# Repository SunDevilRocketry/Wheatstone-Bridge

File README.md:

# L0003 Wheatstone Bridge
Rev 1.0

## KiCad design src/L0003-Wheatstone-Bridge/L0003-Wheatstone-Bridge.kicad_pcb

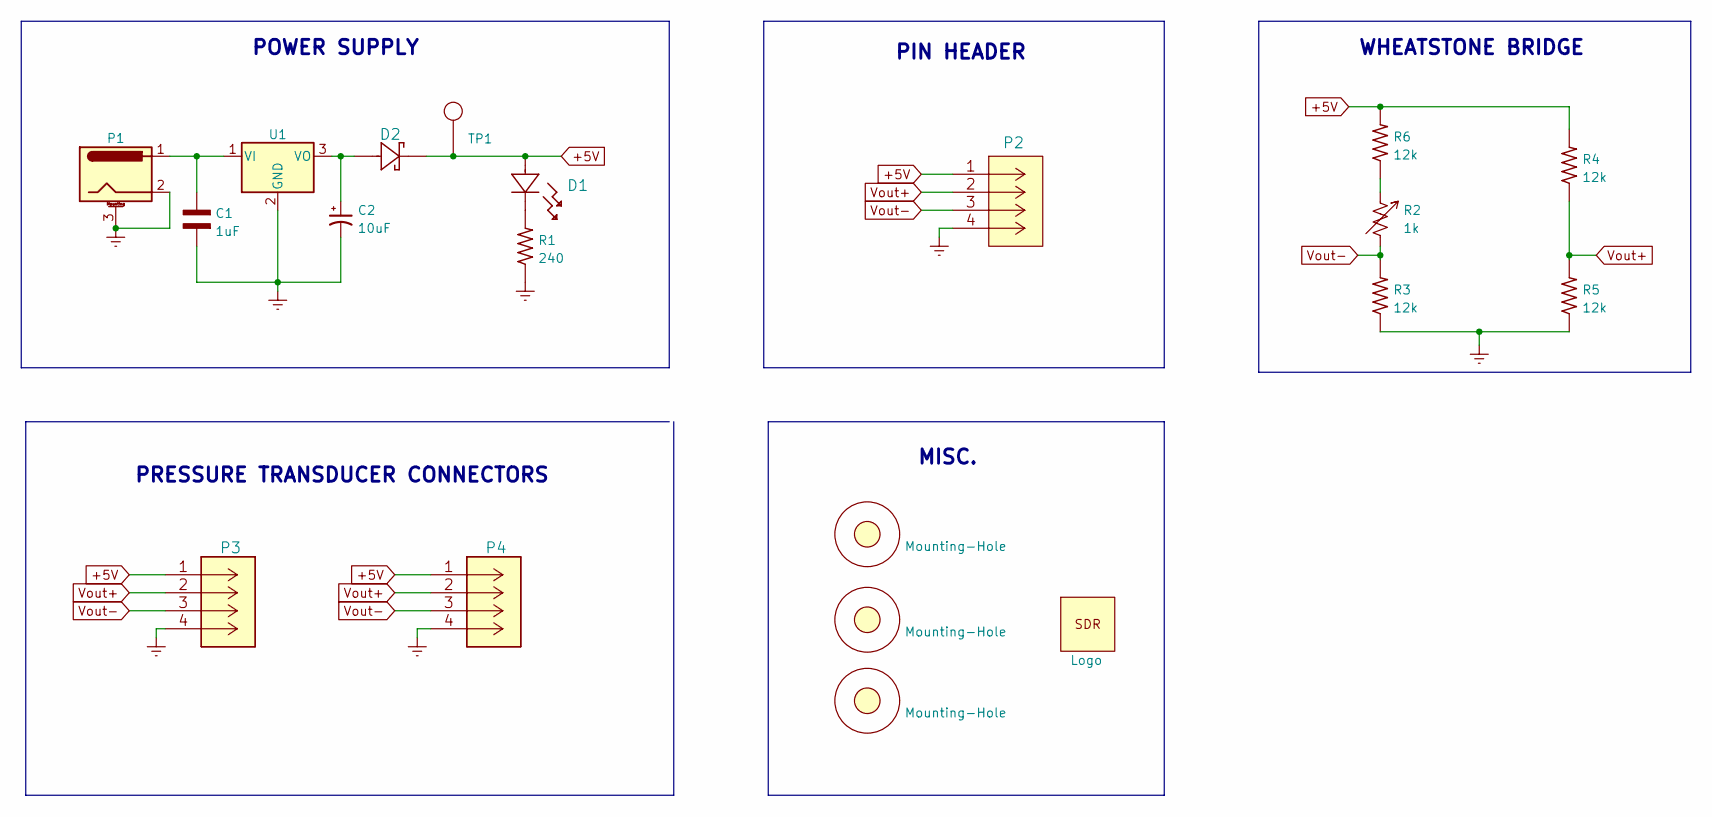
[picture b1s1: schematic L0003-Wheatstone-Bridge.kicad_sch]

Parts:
C1: 1uF
C2: 10uF
D1: SML-LX1206GC-TR
D2: SM5819PL-TP
H1, H2, H3: Mounting-Hole
LOGO1: Logo
P1: EJ508A
P2: PPTC041LFBN-RC
P3, P4: 39299043; CONN_4840.2201_SCH
R1: 240
R2: 1k
R3, R4, R5, R6: 12k
TP1: TP1; TP
U1: MCP1703T-4002E_DB; SOT-223-3_TabPin2

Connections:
+5V: D1.2, D2.1, P2.1, P3.1 (+12V), P4.1 (+12V), R4.2, R6.2, TP1.1
Earth: C1.2, C2.2, P1.2, P1.3 (MountPin), P2.4, P3.4, P4.4, R1.1, R3.1, R5.1, U1.2 (GND)
unnamed: C1.1, P1.1, U1.1 (VI)
unnamed: C2.1, D2.2, U1.3 (VO)
unnamed: D1.1, R1.2
unnamed: R2.1, R6.1
Vout+: P2.2, P3.2 (GND), P4.2 (GND), R4.1, R5.2
Vout-: P2.3, P3.3, P4.3, R2.2, R3.2

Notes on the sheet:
PIN HEADER
MISC.
PRESSURE TRANSDUCER CONNECTORS
WHEATSTONE BRIDGE
POWER SUPPLY

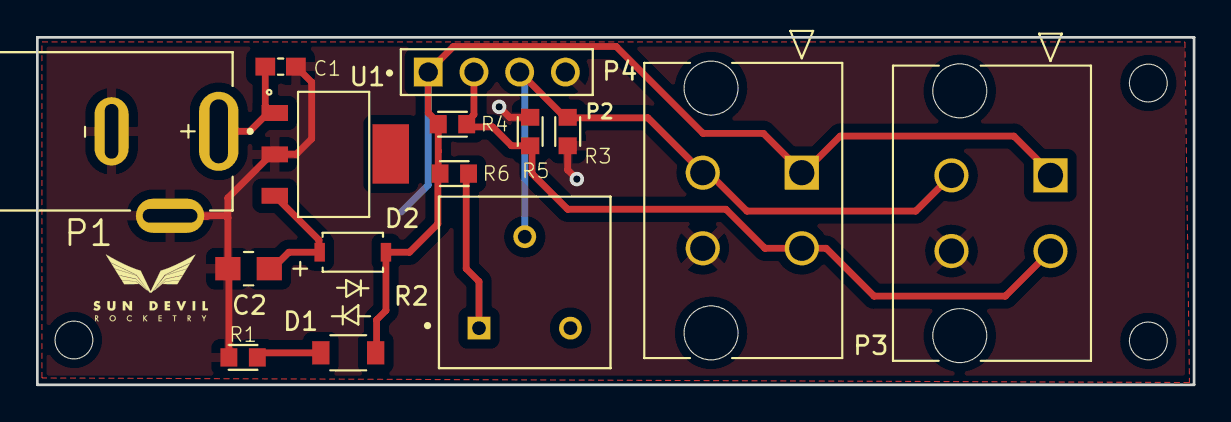
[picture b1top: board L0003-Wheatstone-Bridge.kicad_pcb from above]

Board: 2 copper layers, 64.3 x 19.3 mm, 20 parts (1 on the bottom side), 8 nets.

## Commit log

2021-09-26 created initial directory structure
    Created initial directory structure
2021-09-26 copied library components from local folder
2021-09-26 Added symbols to symbol library
2021-09-26 added 4 pin connector
2021-09-26 Added potentiometer symbol
2021-09-26 added earth symbol to library
2021-09-26 added footprint library
2021-09-27 added footprint library to lib folder
2021-09-27 Added LED and new pin header to footprint library
2021-09-27 Added Green LED to symbol library
2021-10-03 Copied logo, header, and mounting hole symbols into symbol library
2021-10-03 Added pin 3 (invisible, not connected) to potentiometer symbol
2021-10-03 Changed name of potentiometer symbol
2021-10-03 Copied mounting hole and logo footprints
2021-10-03 added 3D files
2021-10-03 moved 3d files into 3d files folder
2021-10-03 changed really long file name to partno
2021-10-08 Made Schematic
2021-10-24 Remade Schematic and Added 240R, Holes, and Logo
2021-10-31 Made circuit look nicer (MISC box & TP points)
2021-11-07 Created PCB Layout
2021-11-07 Finished PCB
2021-11-14 Changed Wire connecting power to VRM
2022-03-05 added production files
2022-03-05 created pdf of schematic
2022-06-12 added PT connectors for engine controller compatibility
2022-07-13 ploted schematic to pdf
2022-09-08 wrote script to calculate important voltage nodes
2022-09-08 updated schematic with new resistor values
2022-09-08 routed rev 3
2022-09-08 generated rev 3.0 gerbers

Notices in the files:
parts and their libraries:
Copyright 2021 Accelerated Designs. All rights reserved.
